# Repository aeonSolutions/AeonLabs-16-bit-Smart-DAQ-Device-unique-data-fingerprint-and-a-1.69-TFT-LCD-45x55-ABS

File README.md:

[ ](https://discord.gg/hw3j3RwfJf)

**Unique Visits** 

</p>

**Navigation** | [AeonLabs Main Index](https://github.com/aeonSolutions/aeonSolutions/blob/main/aeonSolutions-Main-Index.md)  >>   [open Hardware Electronics](https://github.com/aeonSolutions/PCB-Prototyping-Catalogue)  >>  [Laboratory Automation](https://github.com/aeonSolutions/PCB-Prototyping-Catalogue/tree/main/Laboratory%20Automation)  >> Smart DAQs   >> [16-bit Smart DAQs](https://github.com/aeonSolutions/PCB-Prototyping-Catalogue/blob/main/Smart%20DAQ/16-bit/readme.md)   >>  16-bit Smart DAQ Device with unique data fingerprint and a 1.69" TFT LCD 45x55 ABS

<p align="right">
 <a href="https://github-com.translate.goog/aeonSolutions/PCB-Prototyping-Catalogue/tree/main?_x_tr_sl=en&_x_tr_tl=pt&_x_tr_hl=en&_x_tr_pto=wapp">Change Language</a> <br>
Last update: 11-08-2024
</p>

# 16-bit Smart DAQ Device with unique data fingerprint and a 1.69" TFT LCD 45x55 ABS
This is the repository for the 16-bit Smart DAQ Device with a unique data fingerprint able to do experimental data upload to any data repository. This specific hardware electronics utilizes the ADC IC AD5693 from Analog Devices. More information about this ADC IC [here](https://www.analog.com/en/products/ad5693.html). 

<p align="center">
<strong> <a href="https://aeonsolutions.github.io/sponsor/sdad/2ch/">Interactive view of the PCB Layout</a> </strong> &nbsp;
  <strong> <a href="https://aeonsolutions.github.io/sponsor/sdad/2ch/circuit_schematic.html">Interactive view of the circuit schematic</a> </strong> <br>
 <sup>Click to view the latest revision</sup>
</p>

<br>

### rev. 10-2024
status: being designed in KiCad <br>
Known Issues: <br>
- ..

<br>

### rev. 10-2023
status: Fully working <br>
Known Issues: <br>
- PCB copper track optimizations
- components rearrangement for optimization of PCB track inductance 

### rev. 03-2024
This hardware electronics revision has major improvements in the power supply and  also power management improving immensely battery life. It also features USB-C to serial UART communications.

status: Fully working <br>
Known Issues: <br>
- PCB copper track optimizations
- components rearrangement for optimization of PCB track inductance
- poor design of the ground plane on the power management zone of the PCB
- The ultra-deep sleep power management does not work as intended. This is now solved in revision 05-2024.

<br>
<br>

The photo below is one of the many specimens I purposely fabricated to research the self-sensing properties of asphalt mixed with a known content of carbon fibers. This is a 10cm cylinder specimen and on the top is already set up my own design smart #DAQ (get it here on my GitHub ) with the ability to upload LIVE experimental data to a #dataverse. The smart DAQ is installed on an acrylic case and screwed with plastic screws to an acrylic base with the same cross-section area as the specimen to be tested. 

The acrylic base can be bought [here](https://s.click.aliexpress.com/e/_DEGsZaL). And the acrylic case [here](https://s.click.aliexpress.com/e/_Dmudkjt). 

<br>

## Dataverse API C library

This device uses my C++ library to expedite dataverse API integration on smart DAQ devices or elsewhere. Follow the link to its repository:

https://github.com/aeonSolutions/OpenScience-Dataverse-API-C-library

<p align="center">
 
</p>

## CE Ready Logo
This hardware is ready to get a CE marking. To learn more about this marking goto to [Wikipedia here](https://en.wikipedia.org/wiki/CE_marking).

<br>

### Sponsor Open Hardware Solutions 
AeonLabs invests time and resources in providing this open-source hardware electronics. <br>
Did you like any of my PCB KiCad Designs? Help and Support my open work by becoming a GitHub sponsor. Starts with only $1 / 1€.

<p align="center">

</p>

<br>

### Smart PCB Hardware Specifications
The hardware specifications for this 16-bit PCB with dimensions of 23.5x43.5mm can be found [here](https://github.com/aeonSolutions/openScience-Smart-DAQ-to-Upload-Live-Experimental-Data-to-a-Data-Repository/wiki/16‐bit-Smart-DAQ-Hardware-Specifications).

<br>
<br>

 **In real life this smart DAQ is able to:**
- connect to all kinds of 3V to 5V Digital sensors;
- connect to all kinds of sensors compatible with the I2C protocol. (max 118 sensors simultaneously)
- measure voltage in the range of  [0;3.3V]
- measure electrical resistance [0; 10^6] Ohm 
- do temperature and humidity compensation on all measurements 
- has a voltage reference sensor for improved accuracy on ADC measurements  
- has a motion sensor to know if anyone moved a specimen during an experiment
- ability to show live experimental data on the 1.69-inch TFT IPS LCD  

<br>
<br>

## PCB circuit Schematic 
The PCB circuit schematic is available in PDF located in the folder "PCB Schematic"
<br>

## PCB design files
The PCB KiCad files are located in the folder "KiCad" 

<br>
<br>

## Proof of Concept

To test and validate proposed smart DAQ PCB electronics and its firmware as a solution for LIVE experimental data measurements on any test specimen part of an experimental campaign, This PCB electronics is being used to measure a predefined set of variables/parameters to further study several asphalt mixtures with known carbon fiber weight content in the asphalt matrix. Below is a YouTube link to an unedited short video showing one of the experimental setups.

<p align="center">
    
</p>

<br />
<br />

## Author

You can get in touch with me on my LinkedIn Profile:

#### Miguel Tomas

You can also follow my GitHub Profile to stay updated about my latest projects: 

<br>

**Hire me** <br>
See [here](https://github.com/aeonSolutions/PCB-Prototyping-Catalogue/wiki/How-to-Hire-AeonLabs) how to hire AeonLabs.

<br>

### Be supportive of my dedication and work towards technology education and buy me a cup of coffee
The PCB design Files I provide here for anyone to use are free. If you like this Smart Device or use it, please consider buying me a cup of coffee, a slice of pizza or a book to help me study, eat and think new PCB design files.

<p align="center">
    
</p>

### Make a donation on PayPal
Make a donation on PayPal and get a TAX refund*.

<p align="center">
    
</p>

### Support all these open hardware projects and become a GitHub sponsor  
Did you like any of my PCB KiCad Designs? Help and Support my open work to all by becoming a GitHub sponsor.

<p align="center">

</p>

### License

Before proceeding to download any of AeonLabs open source code for software solutions and/or open hardware electronics for smart devices and data acquisition make sure you are choosing the right license for your project. See [AeonLabs Solutions for Open Hardware & Open Source Code](https://github.com/aeonSolutions/PCB-Prototyping-Catalogue/wiki/AeonLabs-Solutions-for-Open-Hardware-&-Source-Development) for more information. For commercial business solutions contact AeonLabs for more information ℹ️ using the contacts above. Thank you 🙏.

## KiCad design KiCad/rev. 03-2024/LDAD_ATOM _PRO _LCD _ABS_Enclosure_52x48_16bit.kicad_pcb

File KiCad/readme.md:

[PCB-Prototyping-Catalogue](https://github.com/aeonSolutions/PCB-Prototyping-Catalogue)  >>  [Laboratory Automation](https://github.com/aeonSolutions/PCB-Prototyping-Catalogue/tree/main/Laboratory%20Automation)  >> S.D.A.D.

<div align="right">
 <a href="https://github-com.translate.goog/aeonSolutions/AeonLabs-AI-Volvo-MKII-Open-Hardware/wiki?_x_tr_sl=en&_x_tr_tl=pt&_x_tr_hl=en&_x_tr_pto=wapp">Change language</a>  <br>
Last change 13-04-2024
</div>

<br>

This folder contains the KiCad Project files for the Smart Data Acquisition Device, the S.D.A.D.,  used on my Open Science projects. Each KiCad project is available with a [creative commons share alike non-commercial license](https://creativecommons.org/licenses/by-nc-sa/4.0/deed.en) . 

<p align="center">
  <strong> <a href="https://aeonsolutions.github.io/portfolio/hardware_electronics/laboratory/">Interactive web view of the PCB Layout</a> </strong> <br>
 <sup>Click to view the latest revision of the PCB Layout</sup>
</p>

However, they're not fully complete. If you like it and are looking to use it on your projects, you can download the complete Kicad project files with a one-time donation, [click here](https://github.com/sponsors/aeonSolutions) to learn how,  and don't forget to include it in a message the name of the module/hardware electronics you need. <br> Thank you 🙏.

### Support all these open hardware projects and become a GitHub sponsor  
Did you like any of my PCB KiCad Designs? Help and Support my open work to all by becoming a GitHub sponsor.

<p align="center">

</p>

#

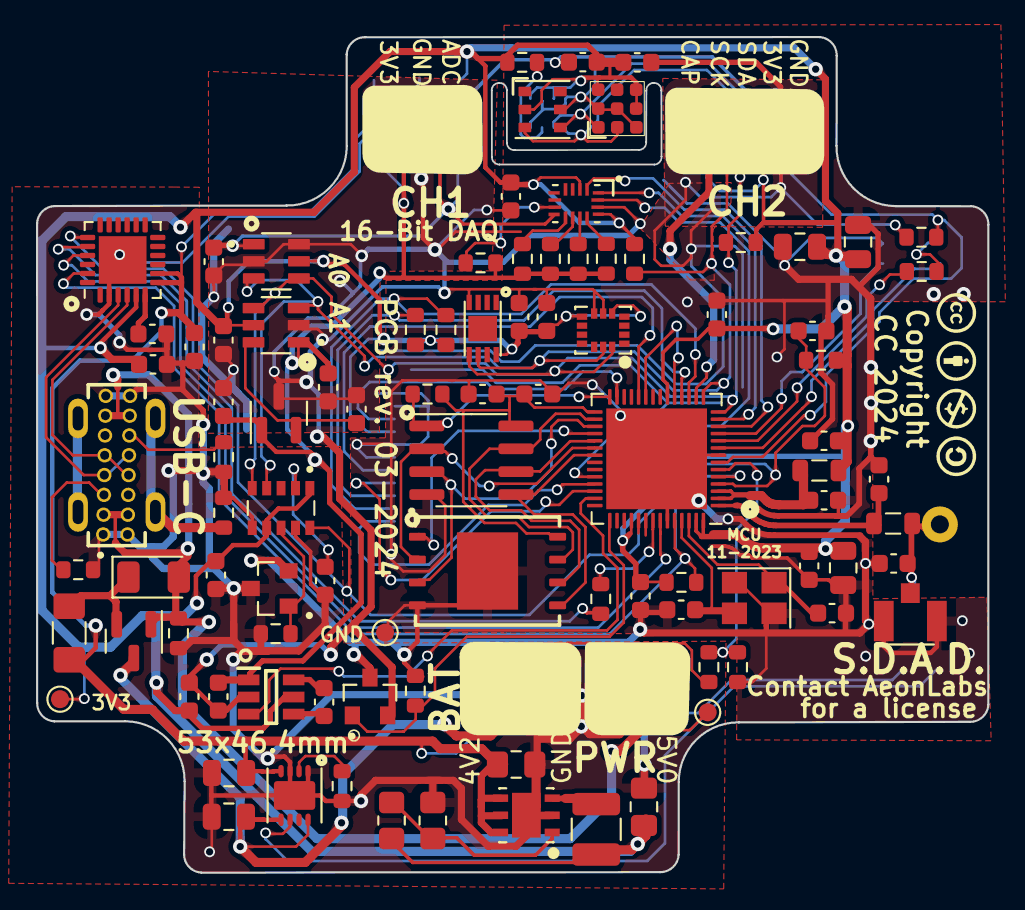
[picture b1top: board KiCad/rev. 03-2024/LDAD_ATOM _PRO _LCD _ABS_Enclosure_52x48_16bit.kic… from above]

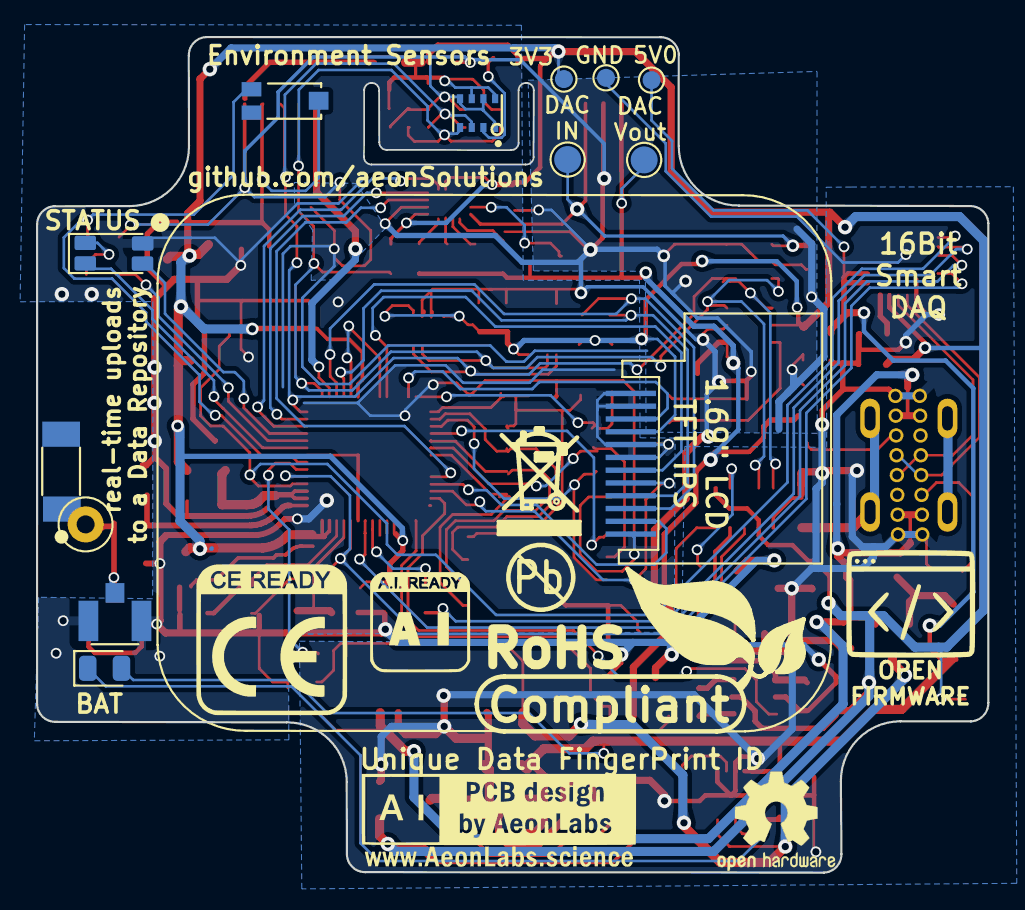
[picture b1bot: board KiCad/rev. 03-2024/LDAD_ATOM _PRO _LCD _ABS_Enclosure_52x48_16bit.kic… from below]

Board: 2 copper layers, 52.9 x 46.4 mm, 111 parts (13 on the bottom side), 70 nets.

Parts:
ADS1100_CH1, ADS1100_CH2: ADS1100A0IDBVR; ADS1100 16-bit ADC SOT95P280X145-6N
ADS1100_CH_C1, ADS1100_CH_C3: 33-100pF; C_0603_1608Metric
ADS1100_CH_C4: 100nF; C_0603_1608Metric
ATSHA_C1: 100nF; C_0603_1608Metric
AUR1: AUR9718x_DFN_3x3mm_6_pin; AUR9718 ST1S09 SON95P300X300X100-7N
AUR_C1: 22uF; C_0805_2012Metric_Pad1.18x1.45mm_HandSolder
AUR_C2: 4.7uF; C_0805_2012Metric_Pad1.18x1.45mm_HandSolder
AUR_R1: 75k; R_0805_2012Metric_Pad1.20x1.40mm_HandSolder
AUR_R2: 24k; R_0805_2012Metric_Pad1.20x1.40mm_HandSolder
AUR_l1: 3.3uF; L_1210_3225Metric
BAT_SENSE_R1, BAT_SENSE_R2: 100k; R_0603_1608Metric
BMPR1: 10k; R_0603_1608Metric
CHC1, CHC2, CHC3: 1uF; C_0603_1608Metric
CN3065_C2: 4.7uF; C_0805_2012Metric
CN3065_R1: 1K8; R_0603_1608Metric
CN3065_STDBY_LED1: LED; LED_0805_2012Metric
CN3965_C1: 22uF; C_0805_2012Metric
DIP_R1: 4k7; R_0603_1608Metric
DIP_R2: 1k; R_0603_1608Metric
DIP_R3: 20k; R_0603_1608Metric
DIP_R4: 200k; R_0603_1608Metric
DIP_R5: 2M; R_0603_1608Metric
DMP1045U_1: DMP1045U; SOT-23
DMP1045_R1: 10K; R_0603_1608Metric
DMP1045_SCHOT1: D_Schottky; D_1206_3216Metric
ENS_C1: 1uF; C_0603_1608Metric
ENS_C2: 100nF; C_0603_1608Metric
EPS1: ESP32-PSRAM_LY68L6400S; SOIC-8_3.9x4.9mm_P1.27mm
ESP32S1: ESP32-S3; QFN-56-1EP_7x7mm_P0.4mm_EP5.6x5.6mm
ESP_FLASH1: W25Q128JVS; WSON8 FLASH SPI SON127P800X600X80-9N
E_DTR_R1: 10k; R_0603_1608Metric
E_LNA_ANT1: SMD-BUILT-IN-ANTENNA-2.4GHZ(2P-9.5X2.1MM); CrossAir CA-C03
E_LNA_ANT2, E_LNA_ANT2#2: U.FL-R-SMT(01); RF Antenna IPEX SMD PCB HRS_U.FL-R-SMT(01)
E_LNA_C1, E_LNA_C2: 2.7pF; C_0603_1608Metric
E_LNA_l1: 1.8nH 5%; L_0805_2012Metric
E_RTS_C1: 100nF; C_0603_1608Metric
E_RTS_R1: 10k; R_0603_1608Metric
E_SPI_C1: 1uF 10% 50V; C_0603_1608Metric
E_SPI_C2: 100nF 10% 16V; C_0603_1608Metric
E_UART_TX_1: 499R; R_0603_1608Metric
E_VDDA_C1: 100nF; C_0603_1608Metric
E_VDDA_C2: 1uF 10% 50V; C_0805_2012Metric
E_VDD_3_C1, E_VDD_3_C2: 10uF 20% 6.3V; C_0805_2012Metric
E_VDD_3_C3, E_VDD_3_C4: 100nF 10% 16V; C_0603_1608Metric
E_VDD_CPU_C1: 100nF 10% 16V; C_0603_1608Metric
E_VDD_L1: 12nH 5%; L_0805_2012Metric
E_VDD_RTC_C1: 100nF 10% 16V; C_0603_1608Metric
E_XTAL40_1: 40Mhz 22pF+-10PPM; Crystal_SMD_3225-4Pin_3.2x2.5mm
E_XTAL40_C1, E_XTAL40_C2: 22pF 5% 50V; C_0603_1608Metric
ExtSWBAT_PLUG2: Conn_01x03_Female; JST_SH_BM03B-SRSS-TB_1x03-1MP_P1.00mm_Vertical
HXC1, HXC2, HXC3: 2.2uF; C_0603_1608Metric
I2C_SCL_R1, I2C_SCL_R2, I2C_SDA_R1, I2C_SDA_R2: 10k; R_0603_1608Metric
IC1: HX4002; HX4002 SOT95 P280X125-6N
IC_ENS1: ENS160 Gas Semsor
IMU1: LSM6DS3; LSM6DS3 Motion Sensor PQFN50P300X250X86-14N
IMUC1: 100nF; C_0603_1608Metric
J2: USB4120-03-C_REVA; USB-C Vertical GCT_USB4120-03-C_REVA
LCD1: Conn_01x12_Male; 1,69 inch LCD IPS TFT
LED1: LED_GBRC; LED_1206_3210_RGB_Metric
LR1: 330R; R_0603_1608Metric
NPN1, NPN2: NPN & PNP SOT-23
NPN1R1, NPN1R3: 10k; R_0603_1608Metric
PLUG1: PLUG1; JST_SH_BM03B-SRSS-TB_1x03-1MP_P1.00mm_Vertical
PLUG2: PLUG2; JST_SH_BM05B-SRSS-TB_1x05-1MP_P1.00mm_Vertical
PSRAM_R1: 100K; R_0603_1608Metric
PWR_FUSE1: Polyfuse; Fuse_1206_3216Metric_Pad1.42x1.75mm_HandSolder
PWR_PLUG1: Screw_Terminal_01x02; JST_SH_BM02B-SRSS-TB_1x02-1MP_P1.00mm_Vertical
RV_C1, RV_C2: 47pF; C_0603_1608Metric
Sign-PbFree: LOGO_PBFREE
Sign-RecycleBin: LOGO_RECYCLEBIN_1
Sign-RoHS: LOGO_ROHS_1
TMPR1: 10K; R_0603_1608Metric
TMUX_C1: 100nF; C_0603_1608Metric
TP1, TP1#2: VIN; TestPoint_Pad_D1.0mm
TP2, TP2#2: VOut; TestPoint_Pad_D1.0mm
TP3, TP3#2: GND; TestPoint_Pad_D1.0mm
U1: MCP1525-TT; SOT-23
U2: ATSHA204A-MAHDA-T; ATSHA204A-MAHDA-T UDFN-8
U3: Battery_charger_CN3065_QFN8; CN3065
U4: AHT20; AHT20 HT Sensor PSON100P300X300X110-6N
U5: CH9102F
U6: TEMT6000; TEMT6000-SEN
U7: BMP280; XDCR_BMP280
U8: TMUX1108RSVR; TMUX1108 1208 multiplexer QFN40P260X180X55-16N
U9: RV-1805-C3_Power_Gating; IC_RV-1805-C3 Power Gating
USB_PLUG_R2, USB_PLUG_R4: 5k1; R_0603_1608Metric
USB_PLYG_R1: 150K; R_0603_1608Metric
VOLTAGE_REF_C1, VOLTAGE_REF_C2: 100nF; C_0603_1608Metric

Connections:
3V3: ADS1100_CH1.5 (VDD), ADS1100_CH2.5 (VDD), ADS1100_CH_C4.2, ATSHA_C1.2, AUR_C1.1, AUR_R1.1, AUR_l1.1, BMPR1.2, CHC3.1, ENS_C1.2, ENS_C2.2, ESP32S1.20 (VDD3P3_RTC), ESP32S1.46 (VDD3P3_CPU), ESP32S1.55 (VDDA), ESP32S1.56 (VDDA), E_DTR_R1.1, E_RTS_R1.1, E_VDDA_C1.2, E_VDDA_C2.2, E_VDD_3_C1.1, E_VDD_3_C2.1, E_VDD_3_C3.1, E_VDD_CPU_C1.1, E_VDD_L1.1, E_VDD_RTC_C1.1, HXC2.2, I2C_SCL_R1.1, I2C_SCL_R2.1, I2C_SDA_R1.2, I2C_SDA_R2.2, IC1.5 (VIN), IC_ENS1.4 (VDD), IC_ENS1.5 (VDDIO), IC_ENS1.7 (CS), IMU1.5 (VDDIO), IMU1.8 (VDD), IMUC1.2, LCD1.4, PLUG2.2, RV_C1.2, TMUX_C1.2, TP2.1, TP2#2.1, U2.8 (VCC), U4.2 (VDD), U5.5 (VIO), U6.COLLECTOR, U7.6 (VDDIO), U7.8 (VDD), U8.2 (EN), U8.13 (VDD), U9.1 (VDD), U9.7 (VBACKUP)
3V3_PLUG: ADS1100_CH2.1 (VIN+), ADS1100_CH_C3.2, DIP_R1.2, DIP_R2.1, DIP_R3.1, DIP_R4.1, DIP_R5.2, HXC3.1, IC1.1 (VOUT), PLUG1.3, U1.1 (Vin), VOLTAGE_REF_C1.2
ADC_CH_V+: ADS1100_CH1.1 (VIN+), ADS1100_CH_C1.2, PLUG1.1, U8.8 (D)
BAT_SENSE_IO21: BAT_SENSE_R1.1, BAT_SENSE_R2.2, ESP32S1.6 (GPIO1/ADC1_CH0)
CAPACITIVE_SENSOR_IO11: ESP32S1.16 (GPIO11/ADC2_CH0), PLUG2.5
CH1_PWR_EN_3V3_IO36: ESP32S1.41 (GPIO36), IC1.3 (EN)
CHIP_EN: ESP32S1.4 (CHIP_PU/RESET), E_RTS_C1.2, E_RTS_R1.2, U5.19 (RTS), U9.10 (~RST)
DAC_CALIBRATION: ESP32S1.19 (GPIO14/ADC2_CH3), ESP32S1.23 (GPIO17/ADC2_CH6/DAC_2)
ESP_GPIO0_BOOT-DTR: ESP32S1.5 (GPIO0/BOOT), ESP32S1.52 (GPIO46), E_DTR_R1.2, U5.23 (DTR)
GND: BAT_SENSE_R1.2, EPS1.4 (VSS), ESP32S1.8 (GPIO3/ADC1_CH2), ESP32S1.51 (GPIO45), ESP32S1.57 (GND), ESP_FLASH1.4 (GND), ESP_FLASH1.9 (GND), E_LNA_ANT2.1 (GND), E_LNA_ANT2.2 (GND), E_LNA_ANT2#2.1 (GND), E_LNA_ANT2#2.2 (GND), E_LNA_C1.2, E_LNA_C2.2, E_RTS_C1.1, E_SPI_C1.2, E_SPI_C2.2, E_VDDA_C1.1, E_VDDA_C2.1, E_VDD_3_C1.2, E_VDD_3_C2.2, E_VDD_3_C3.2, E_VDD_3_C4.2, E_VDD_CPU_C1.2, E_VDD_RTC_C1.2, E_XTAL40_1.2, E_XTAL40_1.4, E_XTAL40_C1.2, E_XTAL40_C2.2, LCD1.1, LCD1.2, LCD1.5, LCD1.6, LCD1.12, LED1.4 (K), NPN1.2, NPN1R3.1, NPN2.3, TP3.1
GNDD: ADS1100_CH1.2 (GND), ADS1100_CH1.6 (VIN-), ADS1100_CH2.2 (GND), ADS1100_CH_C1.1, ADS1100_CH_C3.1, ADS1100_CH_C4.1, ATSHA_C1.1, ENS_C1.1, ENS_C2.1, HXC2.1, HXC3.2, IC1.2 (GND), IC_ENS1.3 (MISO), IC_ENS1.8 (VSS), IC_ENS1.9 (VSS), IMU1.6 (GND), IMU1.7 (GND), IMUC1.1, NPN2.2, PLUG1.2, PLUG2.1, TMPR1.1, TMUX_C1.1, U1.3 (Vss), U2.4 (GND), U4.5 (GND), U7.1 (GND), U7.5 (SDO), U7.7 (GND), U8.14 (GND), VOLTAGE_REF_C1.1, VOLTAGE_REF_C2.1
GNDPWR: AUR1.2 (GND), AUR1.7 (GND), AUR_C1.2, AUR_C2.2, AUR_R2.2, CHC1.2, CHC2.1, CHC3.2, CN3065_C2.1, CN3065_R1.1, CN3965_C1.1, DMP1045_R1.2, ExtSWBAT_PLUG2.3, J2.A1 (GND_A), J2.A12 (GND_A__1), J2.B1 (GND_B), J2.B12 (GND_B__1), NPN1.3, NPN1R1.1, PWR_PLUG1.1, RV_C1.1, RV_C2.1, TP3#2.1, U3.1 (V_Temp), U3.3 (GND), U3.9 (GND), U5.0 (GND), U5.2 (GND), U9.6 (VSS), U9.9 (WDI), USB_PLUG_R2.2, USB_PLUG_R4.2, USB_PLYG_R1.2
GPIO8_I2C_SDA: ADS1100_CH1.4 (SDA), ADS1100_CH2.4 (SDA), ESP32S1.14 (GPIO9/ADC1_CH8), I2C_SDA_R1.1, IC_ENS1.1 (SDA), IMU1.14 (SDA), PLUG2.3, U2.5 (SDA), U4.4 (SDA), U7.3 (SDI), U9.5 (SDA)
GPIO9_I2C_SCL: ADS1100_CH1.3 (SCL), ADS1100_CH2.3 (SCL), ESP32S1.15 (GPIO10/ADC1_CH9), I2C_SCL_R1.2, IC_ENS1.2 (SCL), IMU1.13 (SCL), PLUG2.4, U2.6 (SCL), U4.3 (SCL), U7.4 (SCK), U9.4 (SCL)
LCD_CS_IO36: ESP32S1.40 (GPIO35), LCD1.8
LCD_DC_IO18: ESP32S1.24 (GPIO18/ADC2_CH7/DAC_1), LCD1.7
LCD_I2C_SCL_IO12: ESP32S1.18 (GPIO13/ADC2_CH2), I2C_SCL_R2.2, LCD1.9
LCD_I2C_SDA_IO38: ESP32S1.17 (GPIO12/ADC2_CH1), I2C_SDA_R2.1, LCD1.10
LCD_LED_IO21: ESP32S1.27 (GPIO21), LCD1.3
LCD_RST_IO37: ESP32S1.39 (GPIO34), LCD1.11
LED_B_IO05: ESP32S1.11 (GPIO6/ADC1_CH5), LED1.2 (BA)
LED_G_IO02: ESP32S1.9 (GPIO4/ADC1_CH3), LED1.1 (GA)
LED_R_IO04: ESP32S1.10 (GPIO5/ADC1_CH4), LR1.1
unnamed: AUR1.1 (FB), AUR_R1.2, AUR_R2.1
unnamed: AUR1.3 (SW), AUR_l1.2
unnamed: ESP32S1.1 (LNA_IN/RF), E_LNA_C2.1, E_LNA_l1.2
unnamed: ESP32S1.49 (U0TXD/PROG/GPIO43), E_UART_TX_1.2
unnamed: ESP32S1.2 (VDD3P3), ESP32S1.3 (VDD3P3), E_VDD_3_C4.1, E_VDD_L1.2
unnamed: ESP32S1.53 (XTAL_N), E_XTAL40_1.3, E_XTAL40_C2.1
unnamed: ESP32S1.54 (XTAL_P), E_XTAL40_1.1, E_XTAL40_C1.1
unnamed: E_LNA_ANT1.1, E_LNA_ANT2#2.3 (SIG), E_LNA_C1.1, E_LNA_l1.1
unnamed: HXC1.1, IC1.6 (C+)
unnamed: HXC1.2, IC1.4 (C-)
unnamed: J2.A5 (CC1), USB_PLUG_R2.1
unnamed: J2.B5 (CC2), USB_PLUG_R4.1
unnamed: J2.S1 (SHIELD), USB_PLYG_R1.1
unnamed: LED1.3 (RA), LR1.2
unnamed: CN3065_R1.2, U3.2 (I_SET)
unnamed: CHC2.2, U5.6 (V3)
unnamed: BMPR1.1, U7.2 (CSB)
unnamed: DIP_R1.1, U8.7 (S4)
unnamed: DIP_R2.2, U8.12 (S5)
unnamed: DIP_R3.2, U8.11 (S6)
unnamed: DIP_R4.2, U8.10 (S7)
unnamed: DIP_R5.1, U8.9 (S8)
unnamed: RV_C2.2, U9.2 (CAP_RC)
PERIPHERALS_PWR_EN_IO38: ESP32S1.43 (GPIO38), NPN1R3.2, NPN2.1
PSW_EN: NPN1.1, NPN1R1.2, U9.8 (PSW)
RXD0: ESP32S1.50 (U0RXD/PROG/GPIO44), U5.21 (TXD)
SPICLK: EPS1.6 (SCLK), ESP32S1.33 (SPICLK/GPIO30), ESP_FLASH1.6 (CLK)
SPICS0: ESP32S1.32 (SPICS0/GPIO29), ESP_FLASH1.1 (~CS)
SPICS1: EPS1.1 (~CE), ESP32S1.28 (SPI_CS1/GPIO26), PSRAM_R1.1
SPID: EPS1.5 (SiO0), ESP32S1.35 (SPID/GPIO32), ESP_FLASH1.5 (DI(IO0))
SPIHD: EPS1.7 (SIO3), ESP32S1.30 (SPIHD/GPIO27), ESP_FLASH1.7 (IO3)
SPIQ: EPS1.2 (SIO1), ESP32S1.34 (SPIQ/GPIO31), ESP_FLASH1.2 (DO(IO1))
SPIWP: EPS1.3 (SIO2), ESP32S1.31 (SPIWP/GPIO28), ESP_FLASH1.3 (IO2)
STDBY_LED_G: CN3065_STDBY_LED1.1 (K), U3.6 (LED_DONE)
TEMT6000_IO33: ESP32S1.7 (GPIO2/ADC1_CH1), TMPR1.2, U6.EMITTER
TMUX1208_A0: ESP32S1.12 (GPIO7/ADC1_CH6), U8.1 (A0)
TMUX1208_A1: ESP32S1.13 (GPIO8/ADC1_CH7), U8.16 (A1)
TMUX1208_A2: ESP32S1.38 (GPIO33), U8.15 (A2)
TXD0: E_UART_TX_1.1, U5.20 (RXD)
USB_5V0: DMP1045U_1.1, DMP1045_R1.1, DMP1045_SCHOT1.2 (A), J2.A4 (VBUS_A), J2.A9 (VBUS_A__1), J2.B4 (VBUS_B), J2.B9 (VBUS_B__1), PWR_PLUG1.2, TP1.1
USB_D+: J2.A6 (D1+), J2.B6 (D2+), U5.3 (D+)
USB_D-: J2.A7 (D1-), J2.B7 (D2-), U5.4 (D-)
VDD_SPI: EPS1.8 (VCC), ESP32S1.29 (VDD_SPI), ESP_FLASH1.8 (VCC), E_SPI_C1.1, E_SPI_C2.1, PSRAM_R1.2
VIN: AUR1.4 (VIN_SW), AUR1.5 (VIN_A), AUR1.6 (EN), AUR_C2.1, CHC1.1, CN3065_STDBY_LED1.2 (A), CN3965_C1.2, PWR_FUSE1.1, TP1#2.1, U3.4 (VIN), U5.7 (VDD5), U5.8 (VBUS)
VINF: DMP1045U_1.2, DMP1045_SCHOT1.1 (K), PWR_FUSE1.2
VIN_BAT: BAT_SENSE_R2.1, CN3065_C2.2, DMP1045U_1.3, ExtSWBAT_PLUG2.1, U3.5 (BAT+), U3.8 (FB)
VOLTAGE_REF_2.5V: ADS1100_CH2.6 (VIN-), U1.2 (Vout), VOLTAGE_REF_C2.2

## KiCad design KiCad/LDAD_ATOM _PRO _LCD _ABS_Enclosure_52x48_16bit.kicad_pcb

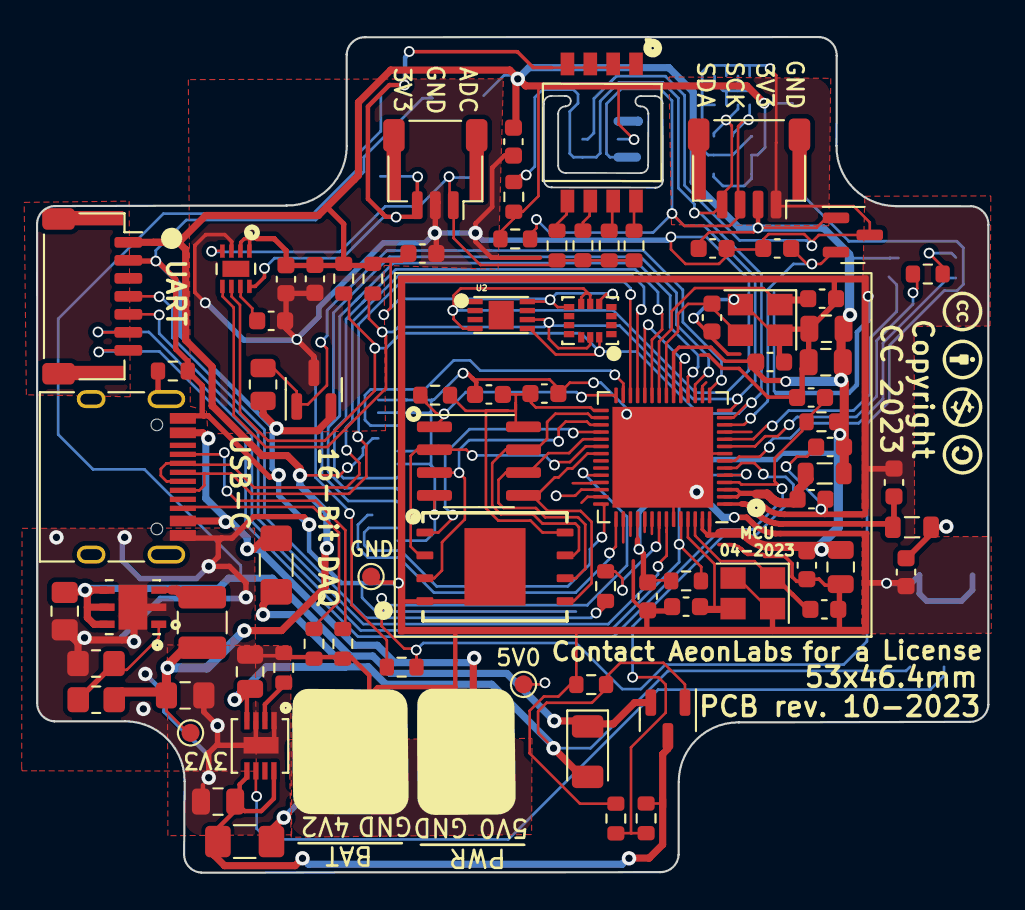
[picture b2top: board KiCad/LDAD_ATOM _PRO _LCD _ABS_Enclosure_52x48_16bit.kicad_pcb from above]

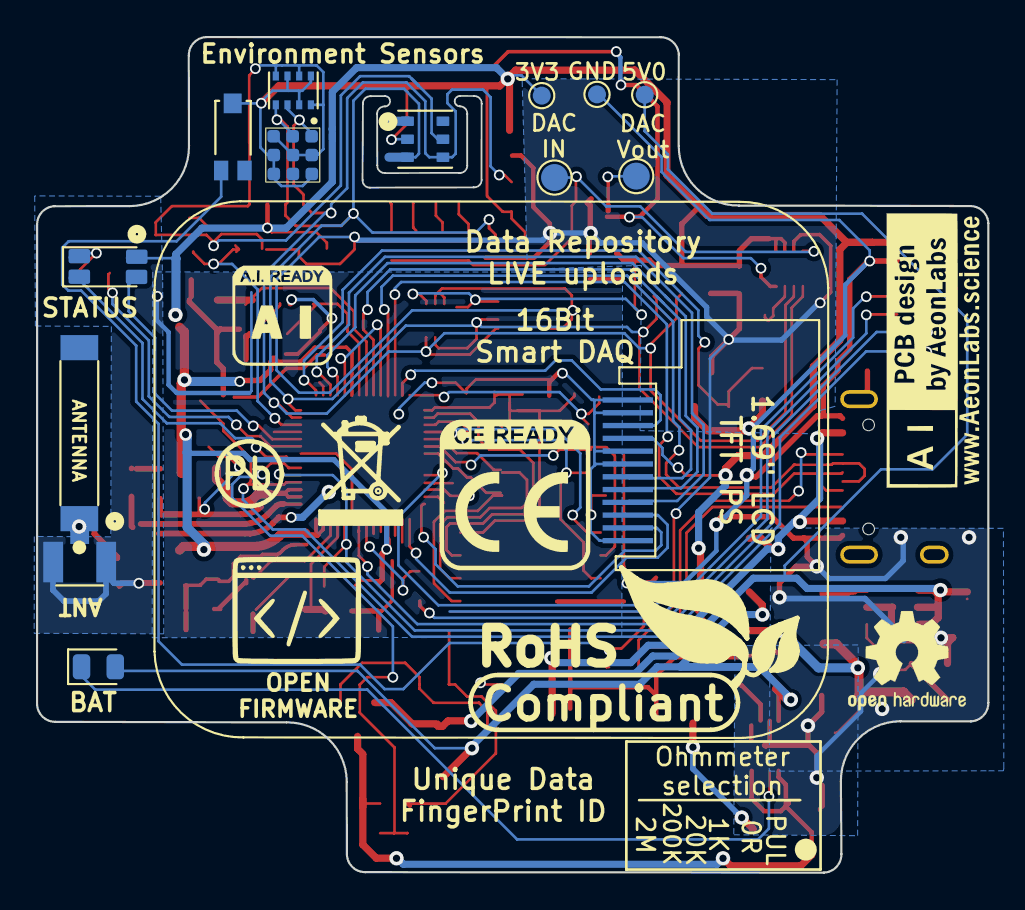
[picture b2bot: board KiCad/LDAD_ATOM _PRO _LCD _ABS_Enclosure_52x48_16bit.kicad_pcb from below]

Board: 2 copper layers, 52.9 x 46.4 mm, 97 parts (15 on the bottom side), 61 nets.

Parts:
ADC16_C1: 100nF; C_0603_1608Metric
ADC16_C2: 10nF; C_0603_1608Metric
ADC16_C3: 10uF; C_0603_1608Metric
ATH20_C2: 100nF; C_0603_1608Metric
ATSHA_C1: 100nF; C_0603_1608Metric
AUR1: AUR9718x_DFN_3x3mm_6_pin; AUR9718 ST1S09 SON95P300X300X100-7N
AUR_C1: 22uF; C_0805_2012Metric_Pad1.18x1.45mm_HandSolder
AUR_C2: 4.7uF; C_0805_2012Metric_Pad1.18x1.45mm_HandSolder
AUR_R1: 75k; R_0805_2012Metric_Pad1.20x1.40mm_HandSolder
AUR_R2: 24k; R_0805_2012Metric_Pad1.20x1.40mm_HandSolder
AUR_l1: 3.3uF; L_1210_3225Metric
BAT_FUSE1: Polyfuse; Fuse_1206_3216Metric_Pad1.42x1.75mm_HandSolder
BAT_SENSE_R1, BAT_SENSE_R2: 100k; R_0603_1608Metric
CN3065_C2: 4.7uF; C_0805_2012Metric
CN3065_R1: 1K8; R_0603_1608Metric
CN3065_STDBY_LED1: LED; LED_0805_2012Metric
CN3965_C1: 22uF; C_0805_2012Metric
DIPSW1: Conn_02x04_Odd_Even; Dip Switch 4pin 1mm
DIP_R2: 1k; R_0603_1608Metric
DIP_R3: 20k; R_0603_1608Metric
DIP_R4: 200k; R_0603_1608Metric
DIP_R5: 2M; R_0603_1608Metric
DMP1045U_1: DMP1045U; SOT-23
DMP1045_R1: 10K; R_0603_1608Metric
DMP1045_SCHOT1: D_Schottky; D_1206_3216Metric
EPS1: ESP32-PSRAM_LY68L6400S; SOIC-8_3.9x4.9mm_P1.27mm
ESP32S1: ESP32-S3; QFN-56-1EP_7x7mm_P0.4mm_EP5.6x5.6mm
ESP32_SHIELD1: RFShield_OnePiece; ESP32-S3 GND Shield
ESP_FLASH1: W25Q128JVS; WSON8 FLASH SPI SON127P800X600X80-9N
E_DTR_R1: 10k; R_0603_1608Metric
E_LNA_ANT1: AN9520; 2.4ghZ WIFI ANTENNA AN9520_ANT2-SMD-9.5X2.1X1.0MM
E_LNA_ANT2: U.FL-R-SMT(01); RF Antenna IPEX SMD PCB HRS_U.FL-R-SMT(01)
E_LNA_C1, E_LNA_C2: 2.7pF; C_0603_1608Metric
E_LNA_l1: 1.8nH 5%; L_0805_2012Metric
E_RTS_C1: 100nF; C_0603_1608Metric
E_RTS_R1: 10k; R_0603_1608Metric
E_SPI_C1: 1uF 10% 50V; C_0603_1608Metric
E_SPI_C2: 100nF 10% 16V; C_0603_1608Metric
E_UART_TX_1: 499R; R_0603_1608Metric
E_VDDA_C1: 100nF; C_0603_1608Metric
E_VDDA_C2: 1uF 10% 50V; C_0805_2012Metric
E_VDD_3_C1, E_VDD_3_C2: 10uF 20% 6.3V; C_0805_2012Metric
E_VDD_3_C3, E_VDD_3_C4: 100nF 10% 16V; C_0603_1608Metric
E_VDD_CPU_C1: 100nF 10% 16V; C_0603_1608Metric
E_VDD_L1: 12nH 5%; L_0805_2012Metric
E_VDD_RTC_C1: 100nF 10% 16V; C_0603_1608Metric
E_XTAL32_1: 32.768Mhz 22pF+-10PPM; Crystal_SMD_3225-4Pin_3.2x2.5mm
E_XTAL32_C1, E_XTAL32_C2, E_XTAL40_C1, E_XTAL40_C2: 22pF 5% 50V; C_0603_1608Metric
E_XTAL40_1: 40Mhz 22pF+-10PPM; Crystal_SMD_3225-4Pin_3.2x2.5mm
ExtSW1: Conn_01x03_Female; JST_SH_SM03B-SRSS-TB_1x03-1MP_P1.00mm_Horizontal
ExtSWBAT_PLUG2: Conn_01x03_Female; JST_SH_SM03B-SRSS-TB_1x03-1MP_P1.00mm_Horizontal
I2C_PLUG1: I2C6; JST_SH_SM04B-SRSS-TB_1x04-1MP_P1.00mm_Horizontal
I2C_SCL_R1, I2C_SDA_R1: 10k; R_0603_1608Metric
IC_ENS1: ENS160 Gas Semsor
IMR1, IMR2: 10K; R_0603_1608Metric
IMU1: LSM6DS3; LSM6DS3 Motion Sensor PQFN50P300X250X86-14N
J1: TYPE-C-31-M-12; USB_C_Receptacle_HRO_TYPE-C-31-M-12
JICSP1: Conn_01x07_Socket; JST_SH_SM07B-SRSS-TB_1x07-1MP_P1.00mm_Horizontal
LCD1: Conn_01x12_Male; 1,69 inch LCD IPS TFT
LED1: LED_GBRC; LED_1206_3210_RGB_Metric
LR1: 330R; R_0603_1608Metric
MTRR1: 10k; R_0805_2012Metric
MTRT1: NPN; SOT-23
PSRAM_R1: 100K; R_0603_1608Metric
PWR_FUSE1: Polyfuse; Fuse_1206_3216Metric_Pad1.42x1.75mm_HandSolder
PWR_PLUG1: Screw_Terminal_01x02; JST_SH_SM02B-SRSS-TB_1x02-1MP_P1.00mm_Horizontal
Sign-PbFree: LOGO_PBFREE
Sign-RecycleBin: LOGO_RECYCLEBIN_1
Sign-RoHS: LOGO_ROHS_1
TMPR1: 10K; R_0603_1608Metric
TP1, TP1#2: VIN; TestPoint_Pad_D1.0mm
TP2, TP2#2: VOut; TestPoint_Pad_D1.0mm
TP3, TP3#2: GND; TestPoint_Pad_D1.0mm
U1: MCP1525-TT; SOT-23
U2: ATSHA204A-MAHDA-T; ATSHA204A-MAHDA-T UDFN-8
U3: Battery_charger_CN3065_QFN8; QFN8 3.1x2.9mm QFNn-8 3x3 SON80P400X400X100-9N
U4: AHT20; AHT20 HT Sensor PSON100P300X300X110-6N
U5: AD5693 16-BIT dac SON50P200X200X60-9N
U6: TEMT6000; TEMT6000-SEN
U7: BMP280; XDCR_BMP280
USB_PLUG_R1, USB_PLUG_R3: 5k1; R_0603_1608Metric
USB_PLYG_R2: 150K; R_0603_1608Metric
VOLTAGE_REF_C1, VOLTAGE_REF_C2: 100nF; C_0603_1608Metric

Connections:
3V3: ADC16_C1.2, ADC16_C3.2, ATH20_C2.2, ATSHA_C1.2, AUR_C1.1, AUR_R1.1, AUR_l1.1, ESP32S1.20 (VDD3P3_RTC), ESP32S1.46 (VDD3P3_CPU), ESP32S1.55 (VDDA), ESP32S1.56 (VDDA), E_DTR_R1.1, E_RTS_R1.1, E_VDDA_C1.2, E_VDDA_C2.2, E_VDD_3_C1.1, E_VDD_3_C2.1, E_VDD_3_C3.1, E_VDD_CPU_C1.1, E_VDD_L1.1, E_VDD_RTC_C1.1, I2C_PLUG1.2, I2C_SCL_R1.1, I2C_SDA_R1.2, IC_ENS1.4 (VDD), IC_ENS1.5 (VDDIO), IC_ENS1.7 (CS), IMR1.1, IMR2.1, IMU1.5 (VDDIO), IMU1.8 (VDD), JICSP1.1, LCD1.4, LED1.4 (K), TP2.1, TP2#2.1, U1.1 (Vin), U2.8 (VCC), U4.2 (VDD), U5.1 (VDD), U5.2 (VLOG), U6.COLLECTOR, U7.2 (CSB), U7.6 (VDDIO), U7.8 (VDD), VOLTAGE_REF_C1.2
ADC_A0: DIP_R2.1, DIP_R3.1, DIP_R4.1, DIP_R5.1, ExtSW1.1, U5.4 (A0)
ADC_VOUT: DIPSW1.1, DIPSW1.3, DIPSW1.5, DIPSW1.7, ExtSW1.3, U5.8 (VOUT)
BAT_SENSE_IO21: BAT_SENSE_R1.1, BAT_SENSE_R2.2, ESP32S1.6 (GPIO1/ADC1_CH0)
CHIP_EN: ESP32S1.4 (CHIP_PU/RESET), E_RTS_C1.2, E_RTS_R1.2, JICSP1.7
DAC_CALIBRATION: ESP32S1.19 (GPIO14/ADC2_CH3), ESP32S1.24 (GPIO18/ADC2_CH7/DAC_1)
ESP_GPIO0_BOOT-DTR: ESP32S1.5 (GPIO0/BOOT), ESP32S1.52 (GPIO46), E_DTR_R1.2, JICSP1.6
GND: AUR1.2 (GND), AUR1.7 (GND), AUR_C1.2, AUR_C2.2, AUR_R2.2, BAT_SENSE_R1.2, CN3065_C2.1, CN3065_R1.1, CN3965_C1.1, DMP1045_R1.2, EPS1.4 (VSS), ESP32S1.8 (GPIO3/ADC1_CH2), ESP32S1.51 (GPIO45), ESP32S1.57 (GND), ESP32_SHIELD1.1 (Shield), ESP_FLASH1.4 (GND), ESP_FLASH1.9 (GND), E_LNA_ANT2.1 (GND), E_LNA_ANT2.2 (GND), E_LNA_C1.2, E_LNA_C2.2, E_RTS_C1.1, E_SPI_C1.2, E_SPI_C2.2, E_VDDA_C1.1, E_VDDA_C2.1, E_VDD_3_C1.2, E_VDD_3_C2.2, E_VDD_3_C3.2, E_VDD_3_C4.2, E_VDD_CPU_C1.2, E_VDD_RTC_C1.2, E_XTAL32_1.2, E_XTAL32_1.4, E_XTAL32_C1.2, E_XTAL32_C2.2, E_XTAL40_1.2, E_XTAL40_1.4, E_XTAL40_C1.2, E_XTAL40_C2.2, ExtSWBAT_PLUG2.3, J1.B1, J1.B12, JICSP1.2, LCD1.1, LCD1.2, LCD1.5, LCD1.6, LCD1.12, MTRR1.1, MTRT1.2, PWR_PLUG1.1, TP3.1, TP3#2.1, U3.1 (V_Temp), U3.3 (GND), U3.9 (GND), USB_PLUG_R1.2, USB_PLUG_R3.2, USB_PLYG_R2.2
GNDD: ADC16_C1.1, ADC16_C2.1, ADC16_C3.1, ATH20_C2.1, ATSHA_C1.1, ExtSW1.2, I2C_PLUG1.1, IC_ENS1.3 (MISO), IC_ENS1.8 (VSS), IC_ENS1.9 (VSS), IMU1.6 (GND), IMU1.7 (GND), MTRT1.3, TMPR1.1, U1.3 (Vss), U2.4 (GND), U4.5 (GND), U5.3 (GND), U7.1 (GND), U7.5 (SDO), U7.7 (GND), VOLTAGE_REF_C1.1, VOLTAGE_REF_C2.1
GPIO8_I2C_SDA: ESP32S1.13 (GPIO8/ADC1_CH7), I2C_PLUG1.4, I2C_SDA_R1.1, IC_ENS1.1 (SDA), IMR1.2, IMU1.14 (SDA), U2.5 (SDA), U4.4 (SDA), U5.6 (SDA), U7.3 (SDI)
GPIO9_I2C_SCL: ESP32S1.14 (GPIO9/ADC1_CH8), I2C_PLUG1.3, I2C_SCL_R1.2, IC_ENS1.2 (SCL), IMR2.2, IMU1.13 (SCL), U2.6 (SCL), U4.3 (SCL), U5.5 (SCL), U7.4 (SCK)
LCD_CS_IO13: ESP32S1.18 (GPIO13/ADC2_CH2), LCD1.8
LCD_DC_IO17: ESP32S1.23 (GPIO17/ADC2_CH6/DAC_2), LCD1.7
LCD_I2C_SCL_IO12: ESP32S1.17 (GPIO12/ADC2_CH1), LCD1.9
LCD_I2C_SDA_IO38: ESP32S1.43 (GPIO38), LCD1.10
LCD_LED_IO21: ESP32S1.27 (GPIO21), LCD1.3
LCD_RST_IO37: ESP32S1.42 (GPIO37), LCD1.11
LED_B_IO05: ESP32S1.10 (GPIO5/ADC1_CH4), LED1.2 (BA)
LED_G_IO02: ESP32S1.7 (GPIO2/ADC1_CH1), LED1.1 (GA)
LED_R_IO04: ESP32S1.9 (GPIO4/ADC1_CH3), LR1.1
unnamed: AUR1.1 (FB), AUR_R1.2, AUR_R2.1
unnamed: AUR1.3 (SW), AUR_l1.2
unnamed: DIPSW1.2, DIP_R2.2
unnamed: DIPSW1.4, DIP_R3.2
unnamed: DIPSW1.6, DIP_R4.2
unnamed: DIPSW1.8, DIP_R5.2
unnamed: ESP32S1.21 (GPIO15/ADC2_CH4/XTAL_32K_P), E_XTAL32_1.3, E_XTAL32_C1.1
unnamed: ESP32S1.22 (GPIO16/ADC2_CH5/XTAL_32K_N), E_XTAL32_1.1, E_XTAL32_C2.1
unnamed: ESP32S1.1 (LNA_IN/RF), E_LNA_C2.1, E_LNA_l1.2
unnamed: ESP32S1.49 (U0TXD/PROG/GPIO43), E_UART_TX_1.2
unnamed: ESP32S1.2 (VDD3P3), ESP32S1.3 (VDD3P3), E_VDD_3_C4.1, E_VDD_L1.2
unnamed: ESP32S1.53 (XTAL_N), E_XTAL40_1.3, E_XTAL40_C2.1
unnamed: ESP32S1.54 (XTAL_P), E_XTAL40_1.1, E_XTAL40_C1.1
unnamed: E_LNA_ANT1.1, E_LNA_ANT2.3 (SIG), E_LNA_C1.1, E_LNA_l1.1
unnamed: J1.A5 (CC1), USB_PLUG_R3.1
unnamed: J1.B5 (CC2), USB_PLUG_R1.1
unnamed: J1.S1 (SHIELD), USB_PLYG_R2.1
unnamed: LED1.3 (RA), LR1.2
unnamed: CN3065_R1.2, U3.2 (I_SET)
unnamed: ADC16_C2.2, U5.7 (VREF)
PERIPHERALS_PWR_EN_IO10: ESP32S1.15 (GPIO10/ADC1_CH9), MTRR1.2, MTRT1.1
RXD0: ESP32S1.50 (U0RXD/PROG/GPIO44), JICSP1.5
SPICLK: EPS1.6 (SCLK), ESP32S1.33 (SPICLK/GPIO30), ESP_FLASH1.6 (CLK)
SPICS0: ESP32S1.32 (SPICS0/GPIO29), ESP_FLASH1.1 (~CS)
SPICS1: EPS1.1 (~CE), ESP32S1.28 (SPI_CS1/GPIO26), PSRAM_R1.1
SPID: EPS1.5 (SiO0), ESP32S1.35 (SPID/GPIO32), ESP_FLASH1.5 (DI(IO0))
SPIHD: EPS1.7 (SIO3), ESP32S1.30 (SPIHD/GPIO27), ESP_FLASH1.7 (IO3)
SPIQ: EPS1.2 (SIO1), ESP32S1.34 (SPIQ/GPIO31), ESP_FLASH1.2 (DO(IO1))
SPIWP: EPS1.3 (SIO2), ESP32S1.31 (SPIWP/GPIO28), ESP_FLASH1.3 (IO2)
STDBY_LED_G: CN3065_STDBY_LED1.1 (K), U3.6 (LED_DONE)
TEMT6000_IO33: ESP32S1.38 (GPIO33), TMPR1.2, U6.EMITTER
TXD0: E_UART_TX_1.1, JICSP1.4
USB_5V0: CN3065_STDBY_LED1.2 (A), CN3965_C1.2, DMP1045U_1.1, DMP1045_R1.1, DMP1045_SCHOT1.2 (A), PWR_FUSE1.1, U3.4 (VIN)
USB_5V0F: J1.A4, J1.A9, PWR_FUSE1.2, PWR_PLUG1.2
USB_D+: ESP32S1.26 (GPIO20/USB_D+/ADC2_CH9), J1.A6 (DP1), J1.B6 (DP2)
USB_D-: ESP32S1.25 (GPIO19/USB_D-/ADC2_CH8), J1.A7 (DN1), J1.B7 (DN2)
VDD_SPI: EPS1.8 (VCC), ESP32S1.29 (VDD_SPI), ESP_FLASH1.8 (VCC), E_SPI_C1.1, E_SPI_C2.1, PSRAM_R1.2
VIN: AUR1.4 (VIN_SW), AUR1.5 (VIN_A), AUR1.6 (EN), AUR_C2.1, DMP1045U_1.2, DMP1045_SCHOT1.1 (K), TP1.1, TP1#2.1
VIN_BAT: BAT_FUSE1.1, BAT_SENSE_R2.1, CN3065_C2.2, DMP1045U_1.3, U3.5 (BAT+), U3.8 (FB)
VIN_BATF: BAT_FUSE1.2, ExtSWBAT_PLUG2.1
VOLTAGE_REF_IO07: ESP32S1.12 (GPIO7/ADC1_CH6), U1.2 (Vout), VOLTAGE_REF_C2.2

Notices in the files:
KiCad/rev. 03-2024/LDAD_ATOM _PRO _LCD _ABS_Enclosure_52x48_16bit.kicad_pcb:
license: creative commons share alike non-commercial
